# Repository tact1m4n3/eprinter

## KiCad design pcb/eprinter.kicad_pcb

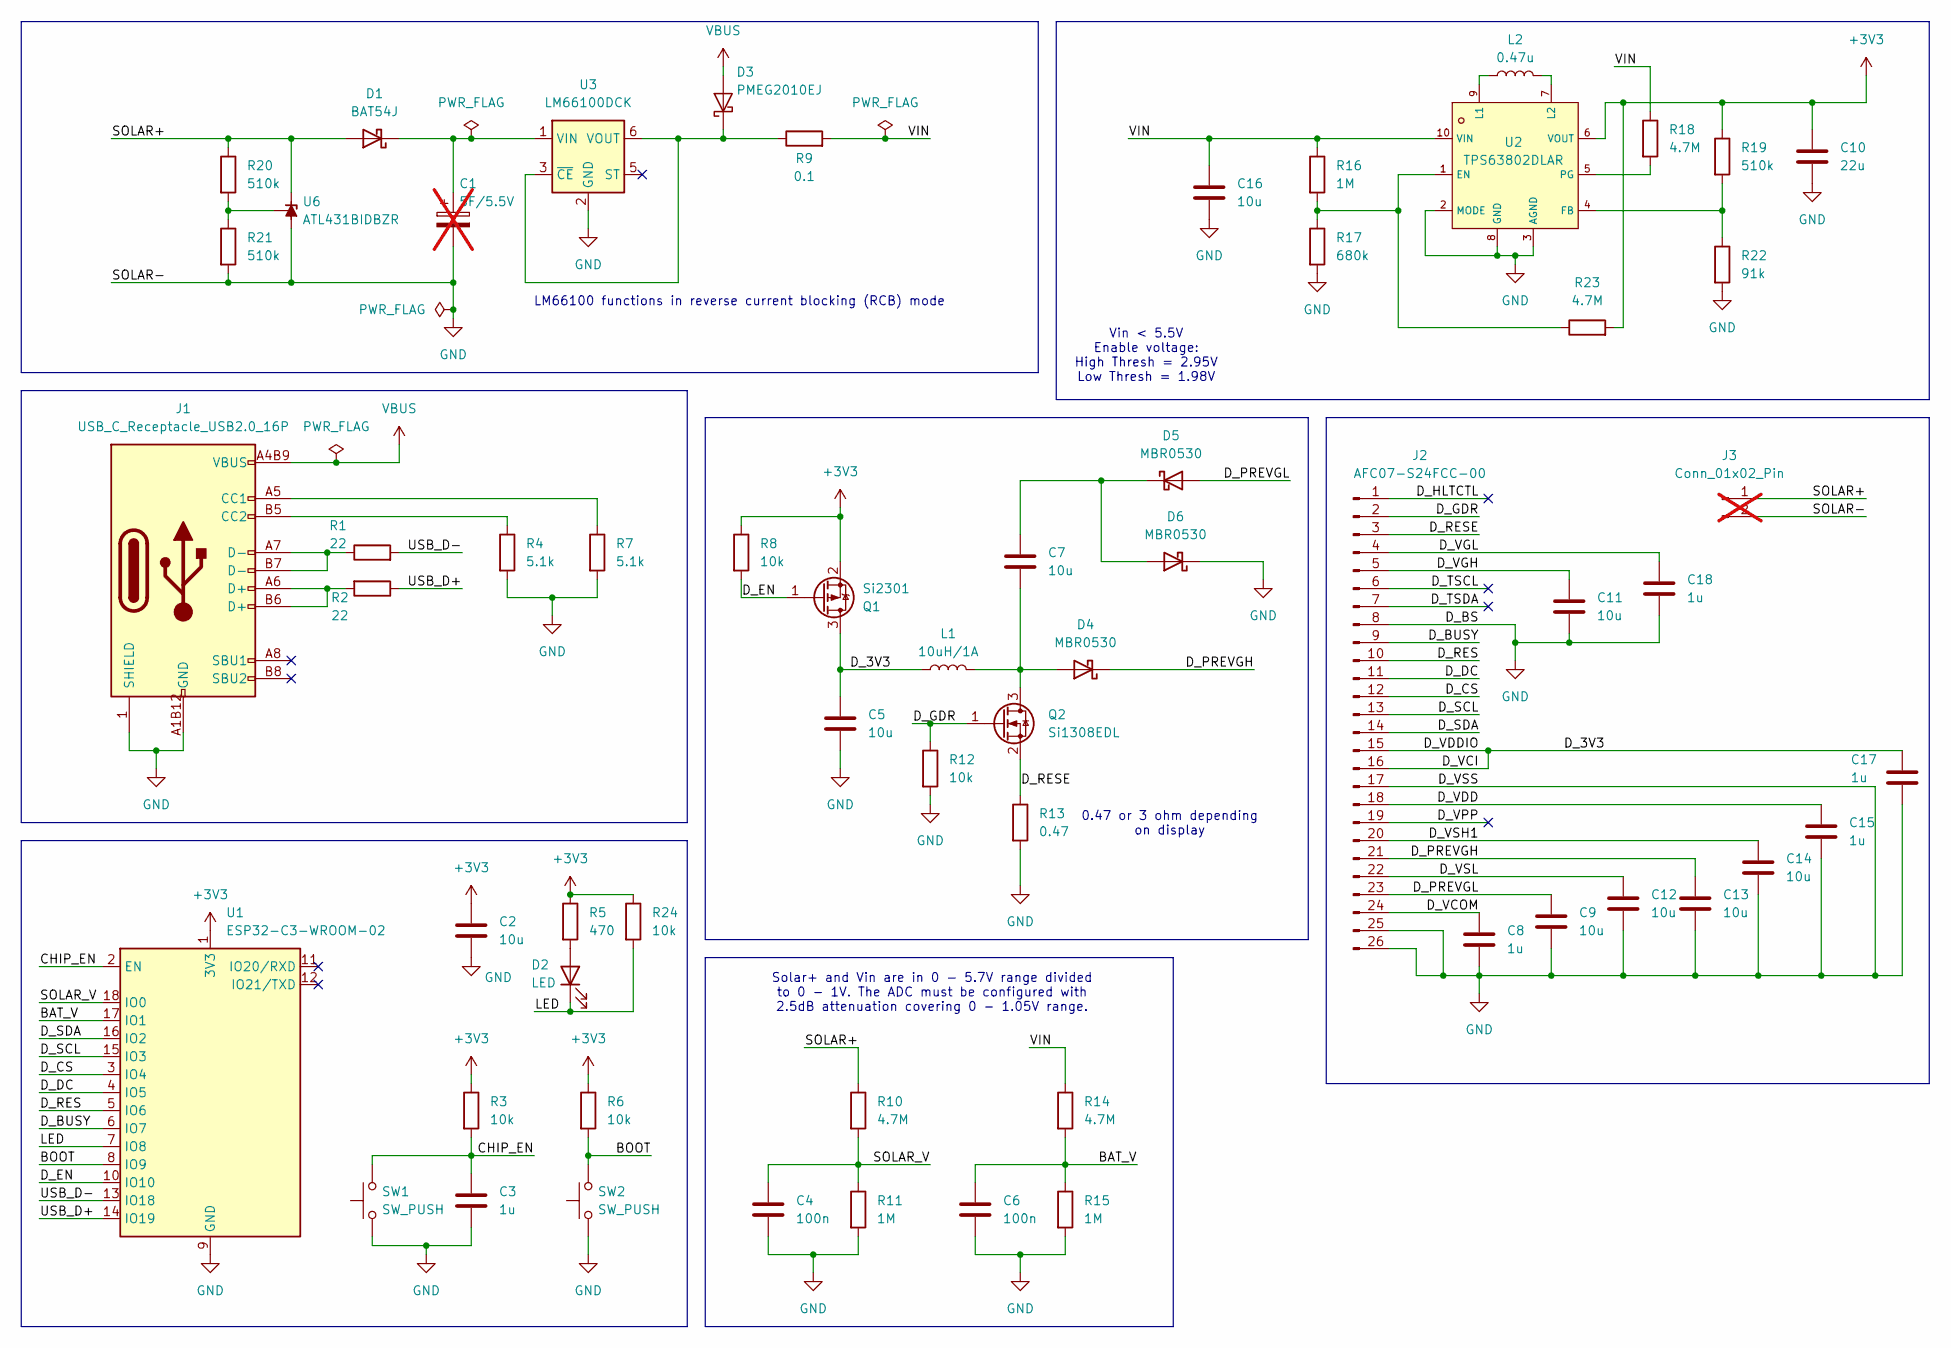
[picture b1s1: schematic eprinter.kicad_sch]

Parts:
C1: 5F/5.5V; THT_SUPERCAP; not fitted
C2, C5, C7, C9, C11, C12, C13, C14, C16: 10u; C_0805_2012Metric; LCSC C440198
C3, C8, C15, C17, C18: 1u; C_0603_1608Metric; LCSC C15849
C4, C6: 100n; C_0603_1608Metric; LCSC C14663
C10: 22u; C_0805_2012Metric; LCSC C45783
D1: BAT54J; D_SOD-323F; LCSC C130415
D2: LED; LED_0603_1608Metric; LCSC C2286
D3: PMEG2010EJ; D_SOD-323F; LCSC C552826
D4, D5, D6: MBR0530; D_SOD-123; LCSC C82046
J1: USB_C_Receptacle_USB2.0_16P; USB-C_SMD-TYPE-C-31-M-12_1; LCSC C165948
J2: AFC07-S24FCC-00; FPC-SMD_AFC07-S24FCC-00; LCSC C11057
J3: Conn_01x02_Pin; PinHeader_1x02_P2.54mm_Vertical; not fitted
L1: 10uH/1A; IND-SMD_L4.0-W4.0; LCSC C2849464
L2: 0.47u; L_1210_3225Metric; LCSC C89029
Q1: Si2301; SOT-23; LCSC C10487
Q2: Si1308EDL; SOT-323_SC-70; LCSC C469327
R1, R2: 22; R_0603_1608Metric; LCSC C23345
R3, R6, R8, R12, R24: 10k; R_0603_1608Metric; LCSC C25804
R4, R7: 5.1k; R_0603_1608Metric; LCSC C23186
R5: 470; R_0603_1608Metric; LCSC C23179
R9: 0.1; R_0603_1608Metric; LCSC C844273
R10, R14, R18, R23: 4.7M; R_0603_1608Metric; LCSC C23163
R11, R15, R16: 1M; R_0603_1608Metric; LCSC C22935
R13: 0.47; R_0603_1608Metric; LCSC C23411
R17: 680k; R_0603_1608Metric; LCSC C25822
R19, R20, R21: 510k; R_0603_1608Metric; LCSC C23192
R22: 91k; R_0603_1608Metric; LCSC C23265
SW1, SW2: SW_PUSH; SW-SMD_L3.9-W3.0-P4.45; LCSC C720477
U1: ESP32-C3-WROOM-02; LCSC C2934560
U2: TPS63802DLAR; VSON-10_L3.0-W2.0-P0.50-TL; LCSC C2845237
U3: LM66100DCK; SOT-363_SC-70-6; LCSC C2869734
U6: ATL431BIDBZR; SOT-23-3; LCSC C701718

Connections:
+3V3: C2.1, C10.1, Q1.2 (S), R3.1, R5.1, R6.1, R8.1, R19.1, R23.2, R24.1, U1.1 (3V3), U2.6 (VOUT)
/BAT_V: C6.1, R14.2, R15.1, U1.17 (IO1)
/BOOT: R6.2, SW2.2, U1.8 (IO9)
/CHIP_EN: C3.1, R3.2, SW1.2, U1.2 (EN)
/D_3V3: C5.1, C17.1, J2.15, J2.16, L1.1, Q1.3 (D)
/D_BUSY: J2.9, U1.6 (IO7)
/D_CS: J2.12, U1.3 (IO4)
/D_DC: J2.11, U1.4 (IO5)
/D_EN: Q1.1 (G), R8.2, U1.10 (IO10)
/D_GDR: J2.2, Q2.1 (G), R12.1
/D_HLTCTL: J2.1
/D_PREVGH: C13.1, D4.1 (K), J2.21
/D_PREVGL: C9.1, D5.2 (A), J2.23
/D_RES: J2.10, U1.5 (IO6)
/D_RESE: J2.3, Q2.2 (S), R13.1
/D_SCL: J2.13, U1.15 (IO3)
/D_SDA: J2.14, U1.16 (IO2)
/D_TSCL: J2.6
/D_TSDA: J2.7
/D_VCOM: C8.1, J2.24
/D_VDD: C15.1, J2.18
/D_VGH: C11.1, J2.5
/D_VGL: C18.1, J2.4
/D_VPP: J2.19
/D_VSH1: C14.1, J2.20
/D_VSL: C12.1, J2.22
/LED: D2.1 (K), R24.2, U1.7 (IO8)
/SOLAR+: D1.2 (A), J3.1, R10.1, R20.1, U6.1 (K)
/SOLAR_V: C4.1, R10.2, R11.1, U1.18 (IO0)
/USB_5V: D3.2 (A), J1.A4B9 (VBUS), J1.B4A9 (VBUS)
/USB_D+: R2.1, U1.14 (IO19)
/USB_D-: R1.2, U1.13 (IO18)
/VIN: C16.1, R9.2, R14.1, R16.1, R18.1, U2.10 (VIN)
GND: C1.2, C2.2, C3.2, C4.2, C5.2, C6.2, C8.2, C9.2, C10.2, C11.2, C12.2, C13.2, C14.2, C15.2, C16.2, C17.2, C18.2, D6.1 (K), J1.1 (SHIELD), J1.2 (SHIELD), J1.3 (SHIELD), J1.4 (SHIELD), J1.A1B12 (GND), J1.B1A12 (GND), J2.8, J2.17, J2.25, J2.26, J3.2, R4.2, R7.2, R11.2, R12.2, R13.2, R15.2, R17.2, R21.2, R22.2, SW1.1, SW2.1, U1.9 (GND), U1.19 (GND), U2.2 (MODE), U2.3 (AGND), U2.8 (GND), U3.2 (GND), U6.3 (A)
unnamed: C1.1, D1.1 (K), U3.1 (VIN)
unnamed: D2.2 (A), R5.2
unnamed: D3.1 (K), R9.1, U3.3 (~CE), U3.6 (VOUT)
unnamed: C7.2, D4.2 (A), L1.2, Q2.3 (D)
unnamed: C7.1, D5.1 (K), D6.2 (A)
unnamed: J1.A5 (CC1), R7.1
unnamed: J1.B5 (CC2), R4.1
unnamed: J1.A6 (D+), J1.B6 (D+), R2.2
unnamed: J1.A7 (D-), J1.B7 (D-), R1.1
unnamed: R16.2, R17.1, R23.1, U2.1 (EN)
unnamed: R19.2, R22.1, U2.4 (FB)
unnamed: L2.1, U2.9 (L1)
unnamed: L2.2, U2.7 (L2)
unnamed: R18.2, U2.5 (PG)
unnamed: R20.2, R21.1, U6.2 (REF)

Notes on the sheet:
Vin < 5.5V Enable voltage: High Thresh = 2.95V Low Thresh = 1.98V
LM66100 functions in reverse current blocking (RCB) mode
0.47 or 3 ohm depending on display
Solar+ and Vin are in 0 - 5.7V range divided to 0 - 1V. The ADC must be configured with 2.5dB attenuation covering 0 - 1.05V range.

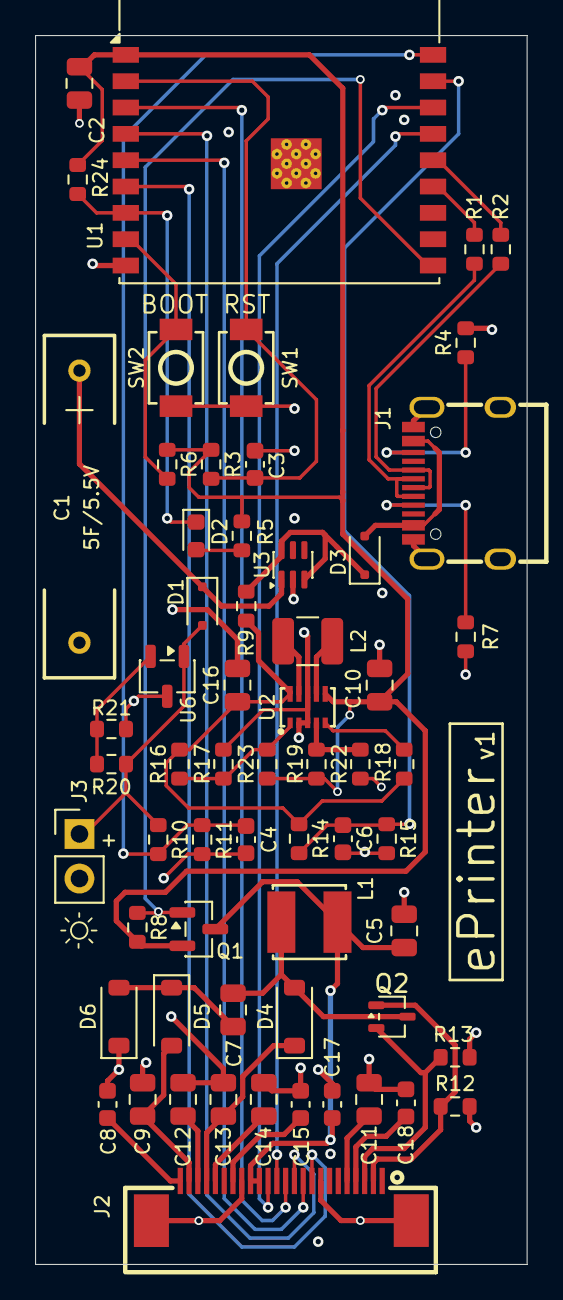
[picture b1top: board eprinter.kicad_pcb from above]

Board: 4 copper layers, 28.0 x 70.0 mm, 61 parts (0 on the bottom side), 45 nets.
